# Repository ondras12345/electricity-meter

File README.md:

# Electricity meter
An STM32-based datalogger for electricity meters with pulse LED.

This repository contains both the PCB design files and firmware source code.

## Features
- detecting pulses of LED more than 100 mm away from the sensor,
- dynamic adjustment of bright / dark threshold,
- logging over one year of 1 minute resolution data to SPI flash,
- command line interface for debugging and reading logged data over USB CDC,
- support for RS485 communication.

## Building
### Hardware
I milled the single sided PCB on my [CNC machine](https://github.com/ondras12345/CNC).

Some notes:
- The DCF-3850N connector is only there for future-proofing. I don't currently
  use it and never tested it.
- The onewire bus connector is currently unused, but it should be easy enough
  to add DS18B20 temperature sensors.
- DS3231 RTC is necessary because the internal RTC on my STM32F103 was not
  accurate enough. Cut JP1 (battery power to STM32 VBAT) if you decide to use
  it too.
- The micro USB connector was a bad idea. I ended up replacing it with wires
  soldered directly to the board after accidentally breaking it off several
  times.

### Firmware
```sh
make help  # show available commands
make  # build
make check  # run cppcheck
```

For uploading to the STM32 via STlink, I use `tools/mkbin` and
`tools/upload_latest`.

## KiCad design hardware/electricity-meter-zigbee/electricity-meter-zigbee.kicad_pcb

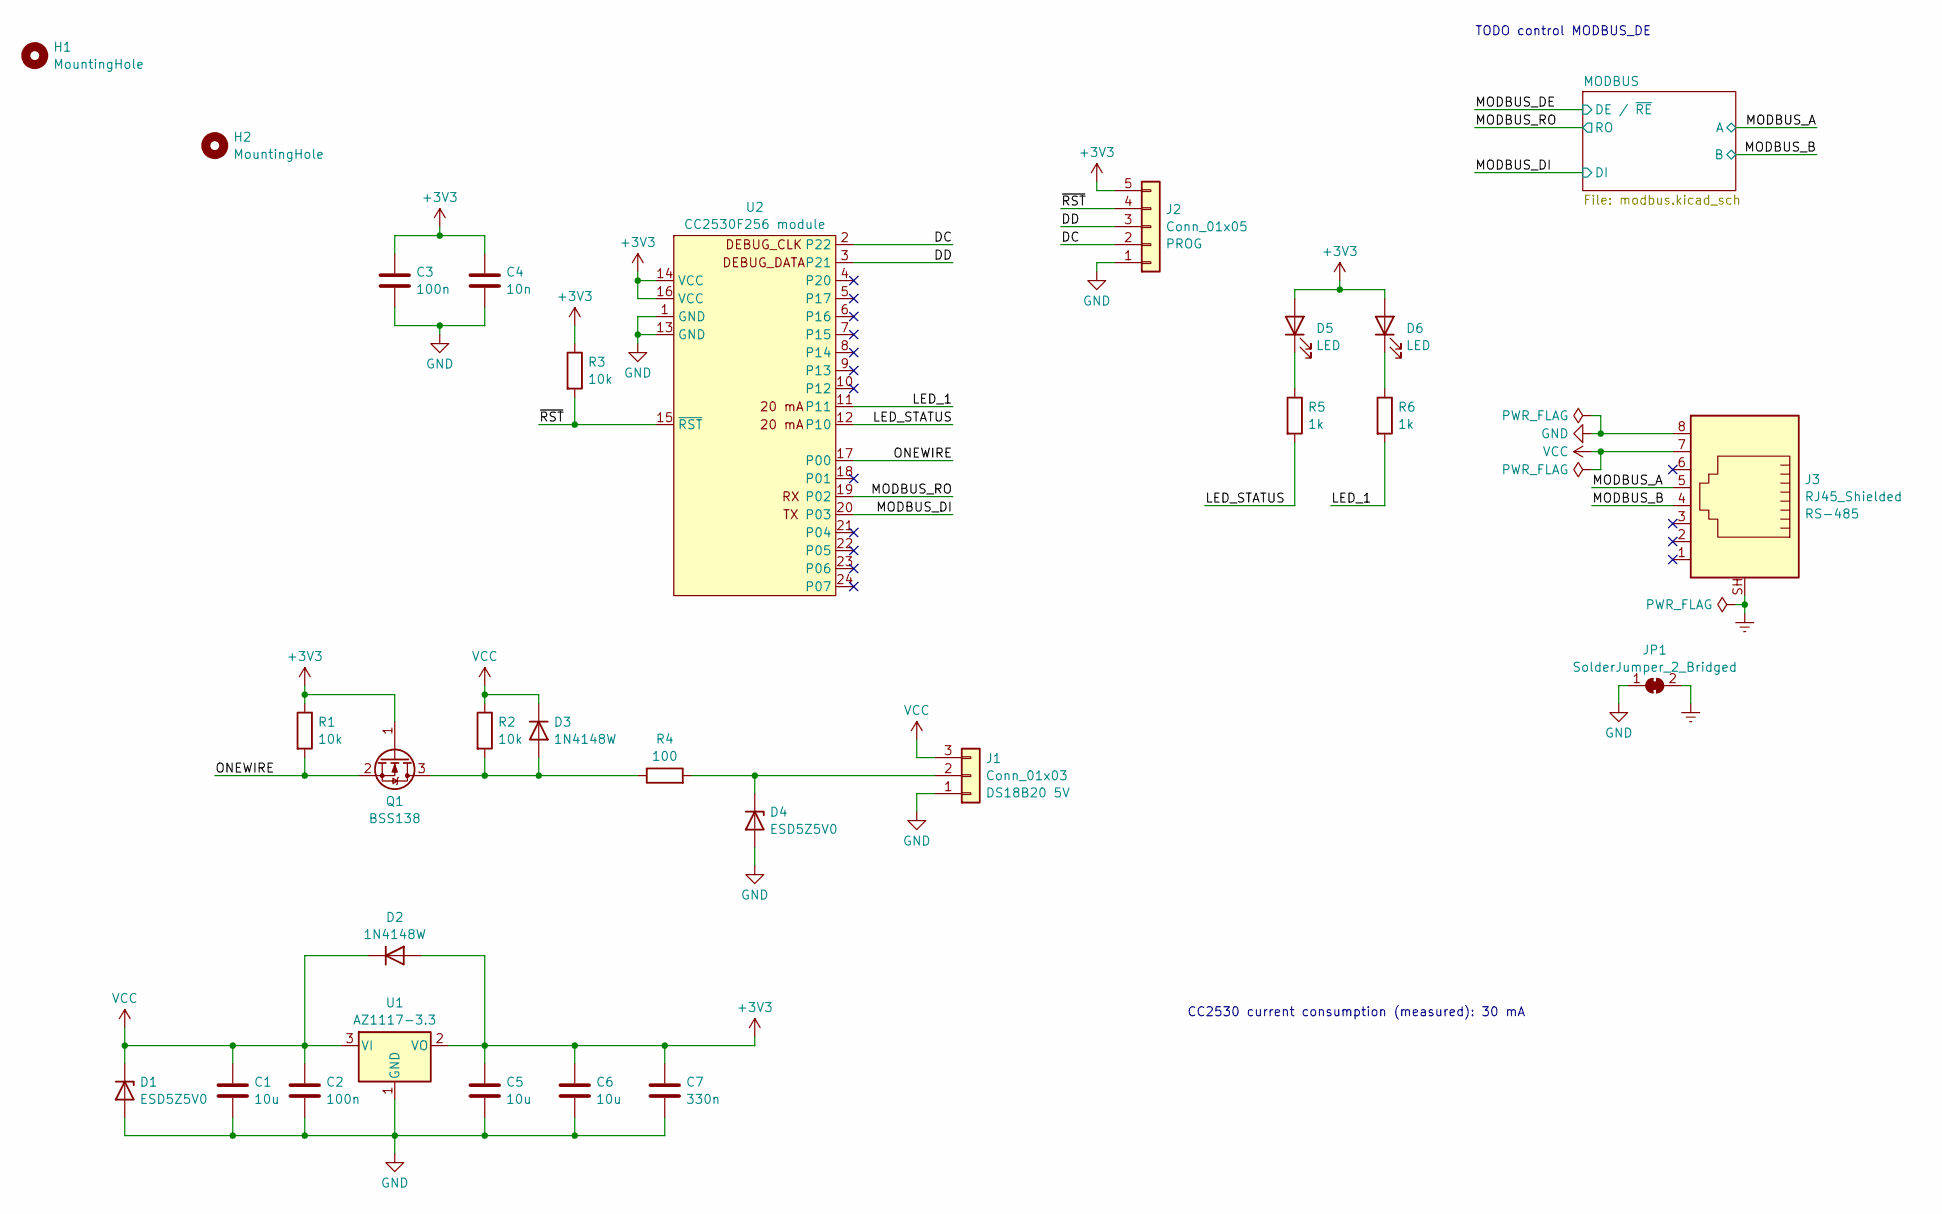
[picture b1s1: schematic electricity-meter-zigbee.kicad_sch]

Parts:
C1, C5, C6: 10u; C_1206_3216Metric_Pad1.33x1.80mm_HandSolder
C2, C3: 100n; C_1206_3216Metric_Pad1.33x1.80mm_HandSolder
C4: 10n; C_1206_3216Metric_Pad1.33x1.80mm_HandSolder
C7: 330n; C_1206_3216Metric_Pad1.33x1.80mm_HandSolder
D1, D4: ESD5Z5V0; D_SOD-523
D2, D3: 1N4148W; D_SOD-123
D5, D6: LED; LED_D3.0mm
H1, H2: MountingHole; MountingHole_3.2mm_M3
J1: Conn_01x03; Molex_KK-254_AE-6410-03A_1x03_P2.54mm_Vertical
J2: Conn_01x05; Molex_KK-254_AE-6410-05A_1x05_P2.54mm_Vertical
J3: RJ45_Shielded; RJ45_HALO_HFJ11-x2450HRL_Horizontal
JP1: SolderJumper_2_Bridged; SolderJumper-2_P1.3mm_Bridged_RoundedPad1.0x1.5mm
Q1: BSS138; SOT-23
R1, R2, R3: 10k; R_1206_3216Metric_Pad1.30x1.75mm_HandSolder
R4: 100; R_1206_3216Metric_Pad1.30x1.75mm_HandSolder
R5, R6: 1k; R_1206_3216Metric_Pad1.30x1.75mm_HandSolder
U1: AZ1117-3.3; SOT-223-3_TabPin2
U2: CC2530F256 module; CC2530F256_module

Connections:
+3V3: C3.1, C4.1, C5.1, C6.1, C7.1, D2.2 (A), D5.2 (A), D6.2 (A), J2.5, Q1.1 (G), R1.1, R3.1, U1.2 (VO), U2.14 (VCC), U2.16 (VCC); also elsewhere on the board
/DC: J2.2, U2.2 (P22)
/DD: J2.3, U2.3 (P21)
/LED_1: R6.2, U2.11
/LED_STATUS: R5.2, U2.12 (P10)
/MODBUS_A: J3.5; also elsewhere on the board
/MODBUS_B: J3.4; also elsewhere on the board
/MODBUS_DI: U2.20 (P03); also elsewhere on the board
/MODBUS_RO: U2.19 (P02); also elsewhere on the board
/ONEWIRE: Q1.2 (S), R1.2, U2.17 (P00)
/~RST: J2.4, R3.2, U2.15 (~RST)
Earth: J3.SH, JP1.2 (B)
GND: C1.2, C2.2, C3.2, C4.2, C5.2, C6.2, C7.2, D1.2 (A), D4.2 (A), J1.1, J2.1, J3.8, JP1.1 (A), U1.1 (GND), U2.1 (GND), U2.13 (GND); also elsewhere on the board
unnamed: D3.2 (A), Q1.3 (D), R2.2, R4.1
unnamed: D4.1 (K), J1.2, R4.2
unnamed: D5.1 (K), R5.1
unnamed: D6.1 (K), R6.1
VCC: C1.1, C2.1, D1.1 (K), D2.1 (K), D3.1 (K), J1.3, J3.7, R2.1, U1.3 (VI)

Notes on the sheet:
TODO control MODBUS_DE
CC2530 current consumption (measured): 30 mA

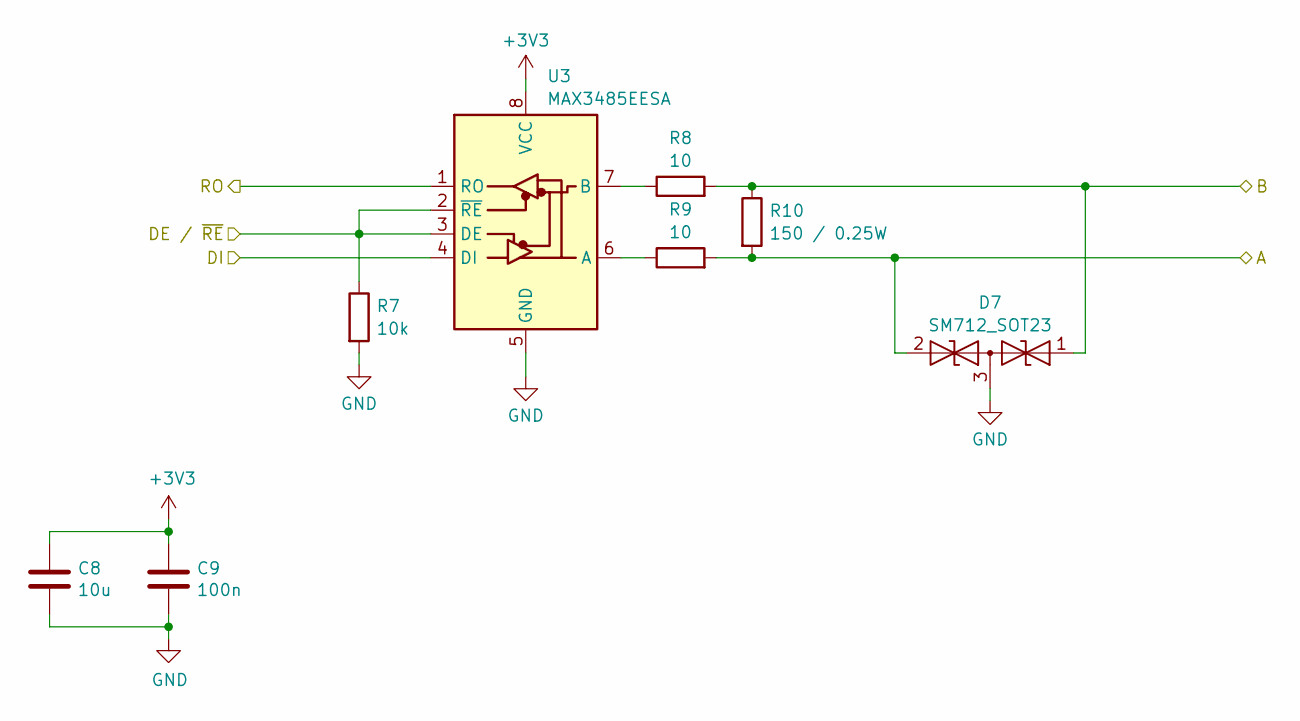
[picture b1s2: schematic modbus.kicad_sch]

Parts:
C8: 10u; C_1206_3216Metric_Pad1.33x1.80mm_HandSolder
C9: 100n; C_1206_3216Metric_Pad1.33x1.80mm_HandSolder
D7: SM712_SOT23; SOT-23
R7: 10k; R_1206_3216Metric_Pad1.30x1.75mm_HandSolder
R8, R9: 10; R_1206_3216Metric_Pad1.30x1.75mm_HandSolder
R10: 150 / 0.25W; R_1206_3216Metric_Pad1.30x1.75mm_HandSolder
U3: MAX3485EESA; SO-8_3.9x4.9mm_P1.27mm

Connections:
+3V3: C8.1, C9.1, U3.8 (VCC); also elsewhere on the board
/MODBUS_A: D7.2 (A2), R9.2, R10.2; also elsewhere on the board
/MODBUS_B: D7.1 (A1), R8.2, R10.1; also elsewhere on the board
/MODBUS_DE: R7.1, U3.2 (~RE), U3.3 (DE)
/MODBUS_DI: U3.4 (DI); also elsewhere on the board
/MODBUS_RO: U3.1 (RO); also elsewhere on the board
GND: C8.2, C9.2, D7.3 (common), R7.2, U3.5 (GND); also elsewhere on the board
unnamed: R9.1, U3.6 (A)
unnamed: R8.1, U3.7 (B)

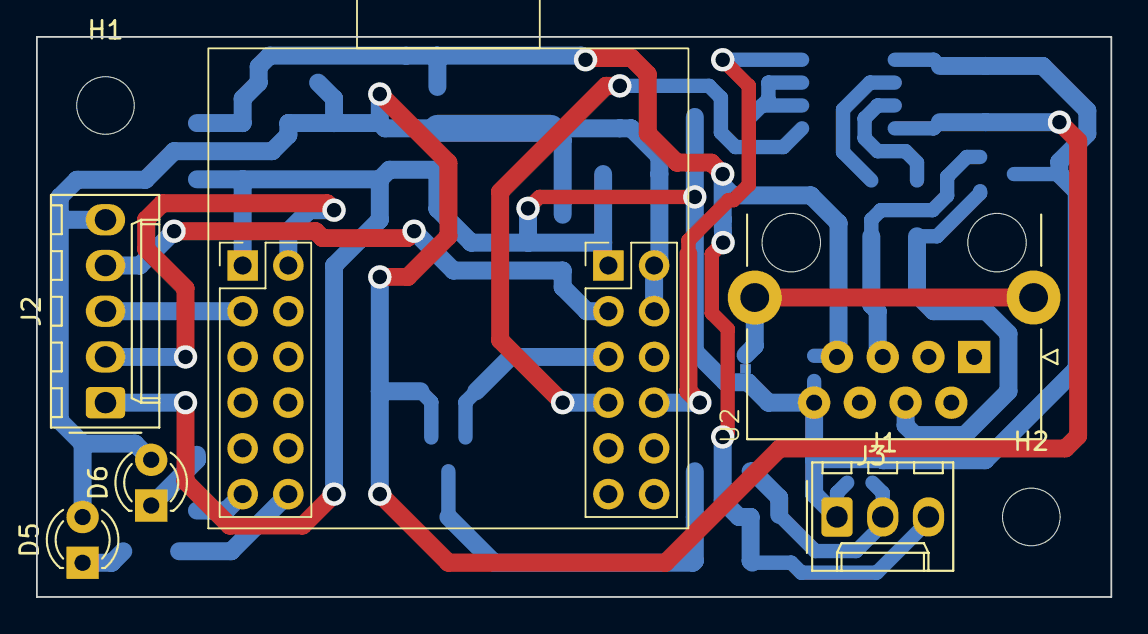
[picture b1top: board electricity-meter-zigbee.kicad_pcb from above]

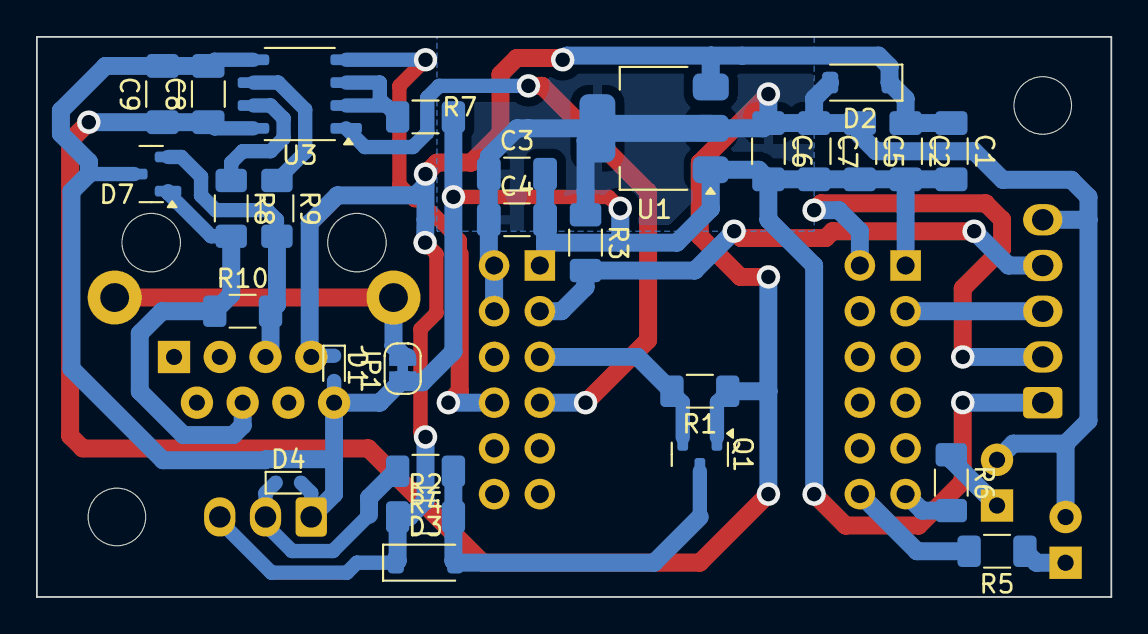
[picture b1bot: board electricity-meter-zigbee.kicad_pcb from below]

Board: 2 copper layers, 59.7 x 31.1 mm, 36 parts (28 on the bottom side), 21 nets.

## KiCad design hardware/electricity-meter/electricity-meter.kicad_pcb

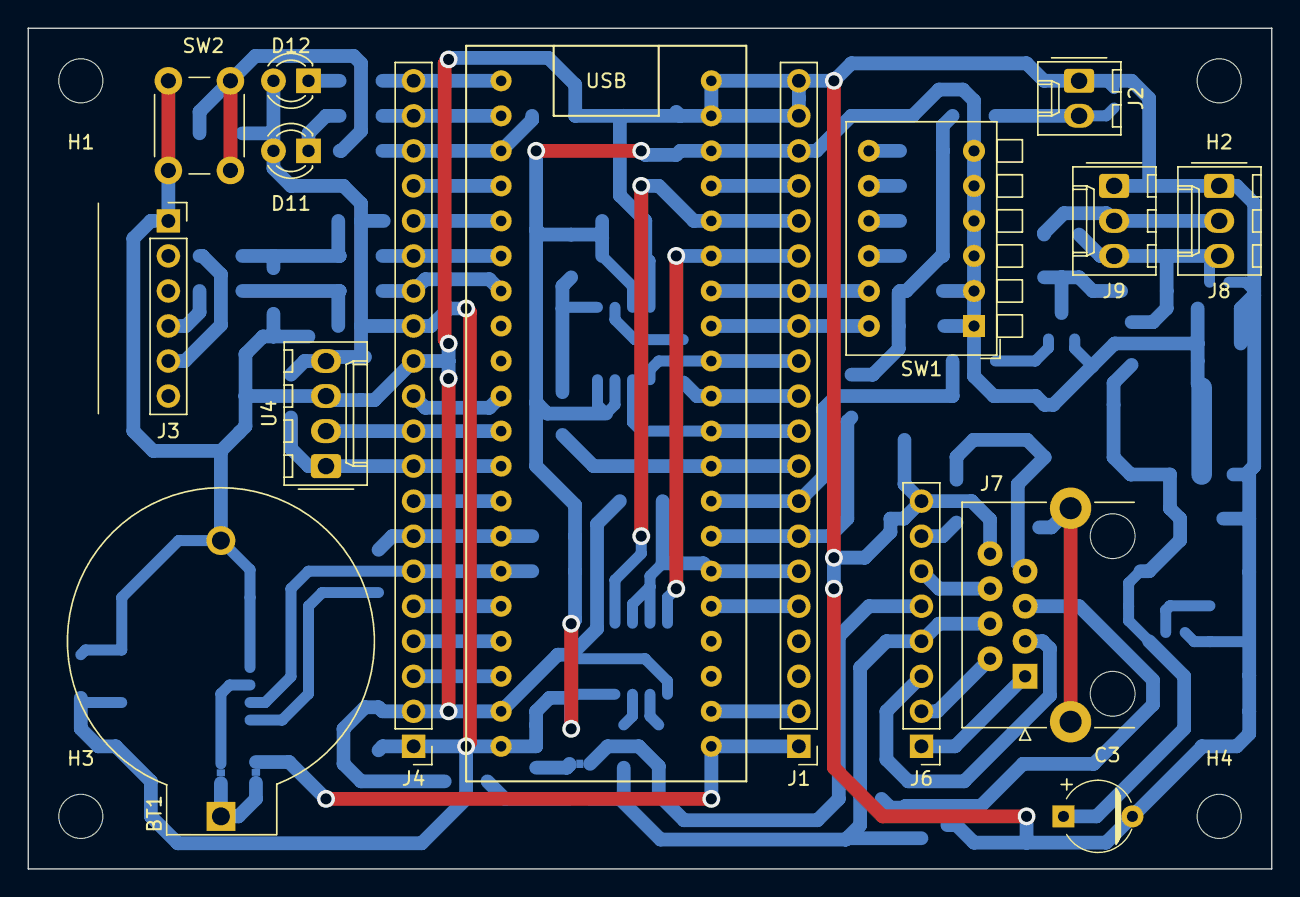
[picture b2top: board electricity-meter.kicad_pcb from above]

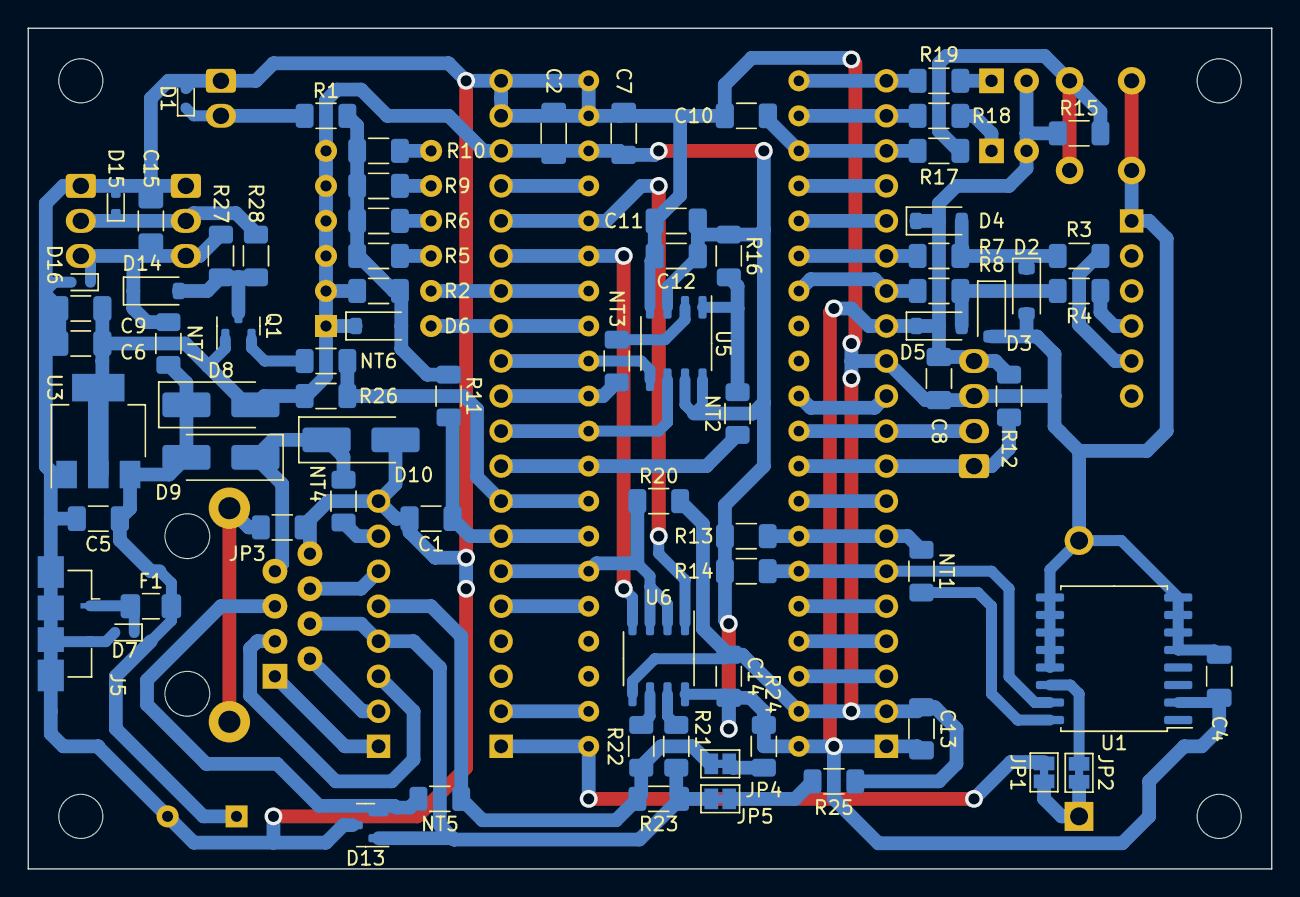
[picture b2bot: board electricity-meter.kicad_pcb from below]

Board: 2 copper layers, 90.2 x 61.0 mm, 95 parts (75 on the bottom side), 71 nets.

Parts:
BT1: CR2032; BatteryHolder_DS1092-04-B6P
C1: 10n; C_1206_3216Metric_Pad1.33x1.80mm_HandSolder
C2, C4, C5, C8, C10, C12, C14, C15: 100n; C_1206_3216Metric_Pad1.33x1.80mm_HandSolder
C3: 100u; CP_Radial_D5.0mm_P5.00mm
C6, C7, C11, C13: 10u; C_1206_3216Metric_Pad1.33x1.80mm_HandSolder
C9: 330n; C_1206_3216Metric_Pad1.33x1.80mm_HandSolder
D1: ESD5Z3.3T1G; D_SOD-523
D2, D3, D4, D5, D6, D14: 1N4148W; D_SOD-123
D7, D15, D16: ESD5Z5V0; D_SOD-523
D8, D9, D10: 1N4007; D_SMA_Handsoldering
D11: YELLOW; LED_D3.0mm
D12: GREEN; LED_D3.0mm
D13: SM712_SOT23; SOT-23
F1: 0ZCJ0016FF2E; Fuse_1206_3216Metric_Pad1.42x1.75mm_HandSolder
H1, H2, H3, H4: MountingHole; MountingHole_3.2mm_M3
J1, J4: Conn_01x20_Pin; PinHeader_1x20_P2.54mm_Vertical
J2: Conn_01x02_Pin; Molex_KK-254_AE-6410-02A_1x02_P2.54mm_Vertical
J3: FTDI breakout; FTDI_breakout
J5: ESB228110100Z; USB_Micro-B_Amphenol_10104110_Horizontal_power_only
J6: Conn_01x08; PinHeader_1x08_P2.54mm_Vertical
J7: RJ45_Shielded; RJ45_HALO_HFJ11-x2450HRL_Horizontal
J8, J9: Conn_01x03; Molex_KK-254_AE-6410-03A_1x03_P2.54mm_Vertical
JP1, JP2, JP4, JP5: SolderJumper_2_Bridged; SolderJumper-2_P1.3mm_Bridged_Pad1.0x1.5mm
JP3: SolderJumper_2_Bridged; R_1206_3216Metric_Pad1.30x1.75mm_HandSolder
NT1, NT2, NT3, NT4, NT5, NT6, NT7: NetTie_2; R_1206_3216Metric_Pad1.30x1.75mm_HandSolder
Q1: BSS138; SOT-23
R1, R3, R4: 1k; R_1206_3216Metric_Pad1.30x1.75mm_HandSolder
R2, R5: 330k; R_1206_3216Metric_Pad1.30x1.75mm_HandSolder
R6: 100k; R_1206_3216Metric_Pad1.30x1.75mm_HandSolder
R7, R8: 100; R_1206_3216Metric_Pad1.30x1.75mm_HandSolder
R9: 33k; R_1206_3216Metric_Pad1.30x1.75mm_HandSolder
R10, R12, R15, R16, R17, R20, R26, R27: 10k; R_1206_3216Metric_Pad1.30x1.75mm_HandSolder
R11, R18, R19, R24, R25: 330; R_1206_3216Metric_Pad1.30x1.75mm_HandSolder
R13, R14: 2k2; R_1206_3216Metric_Pad1.30x1.75mm_HandSolder
R21, R22, R28: 10; R_1206_3216Metric_Pad1.30x1.75mm_HandSolder
R23: 150 / 0.25W; R_1206_3216Metric_Pad1.30x1.75mm_HandSolder
SW1: SW_DIP_x06; SW_DIP_SPSTx06_Piano_10.8x16.8mm_W7.62mm_P2.54mm
SW2: SW_Push; SW_PUSH_6mm
U1: DS3231M; SOIC-16W_7.5x10.3mm_P1.27mm
U2: ChinaBluePill
U3: AZ1117-3.3; SOT-223-3_TabPin2
U4: DCF-3850N-800; Molex_KK-254_AE-6410-04A_1x04_P2.54mm_Vertical
U5: MX25L3233FM1; SOP-8_3.9x4.9mm_P1.27mm
U6: MAX3485EESA; SO-8_3.9x4.9mm_P1.27mm

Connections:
+3V3: C2.1, C4.1, C6.1, C7.1, C8.1, C9.1, C11.1, C12.1, C13.1, C14.1, D4.1 (K), D5.1 (K), D6.1 (K), D8.2 (A), D11.2 (A), D12.2 (A), J1.18, J4.1, J4.13, Q1.1 (G), R2.1, R12.1, R13.1, R14.1, R15.1, R16.1, R24.1, R26.1, SW1.1, SW1.2, SW1.3, SW1.4, SW1.5, SW1.6, U1.2 (VCC), U2.3V3, U3.2 (VO), U4.4 (VDD), U5.3 (~WP/SIO2), U5.7 (~HOLD/SIO3), U5.8 (VCC), U6.8 (VCC)
+5V: C3.1, C5.1, D8.1 (K), D9.2 (A), F1.2, NT7.2, U3.3 (VI)
/5V_STM: J4.3, U2.5V
/BTN_UMOUNT: C10.1, J4.18, R17.1, U2.PB14
/DCF77_DATA: J4.10, U2.PB3, U4.2 (OUT)
/DCF77_~PON: J4.9, R12.2, U2.PB4, U4.1 (~PON)
/LED_PULSE: J4.19, R18.2, U2.PB13
/LED_STATUS: J4.20, R19.2, U2.PB12
/MISO: J1.11, NT3.1, U2.PA6
/MODBUS_A: D13.2 (A2), J7.5, NT5.2
/MODBUS_A_NT: J6.5, JP4.1 (A), NT5.1, R22.2, R23.2
/MODBUS_B: D13.1 (A1), J6.4, J7.4, JP5.2 (B), R21.2, R23.1
/MODBUS_DE: J1.6, R20.1, U2.PA1, U6.2 (~RE), U6.3 (DE)
/MODBUS_DI: J1.15, U2.PB10, U6.4 (DI)
/MODBUS_RO: J1.16, U2.PB11, U6.1 (RO)
/MODBUS_VP: D9.1 (K), D10.1 (K), J7.7, NT4.2
/MOSI: J1.12, U2.PA7, U5.5 (SI/SIO0)
/NRST: J1.17, U2.NRST
/ONEWIRE: J1.8, NT6.1, R26.2, U2.PA3
/PA0: J1.5, U2.PA0
/PA2: C1.1, J1.7, R11.2, U2.PA2
/PA4: J1.9, NT2.1, U2.PA4
/PA5: J1.10, U2.PA5, U5.6 (SCLK)
/PA8: J4.16, U2.PA8
/PA9: J4.15, R7.2, U2.PA9
/PA10: J4.14, R8.2, U2.PA10
/PA15: J4.11, U2.PA15
/PB0: J1.13, SW1.12, U2.PB0
/PB1: J1.14, SW1.11, U2.PB1
/PB5: J4.8, U2.PB5
/PB6: J4.7, NT1.1, R13.2, U2.PB6
/PB7: J4.6, R14.2, U1.15 (SDA), U2.PB7
/PB8: J4.5, U2.PB8
/PB9: J4.4, U2.PB9
/PB15: J4.17, U2.PB15
/PC13: J1.2, U2.PC13
/VBAT: J1.1, JP1.2 (B), U2.VBAT
/onewire/ONEWIRE_5V: D14.2 (A), Q1.3 (D), R27.2, R28.1
Earth: J7.SH, JP3.2 (B)
GND: BT1.2 (-), C1.2, C2.2, C3.2, C4.2, C5.2, C6.2, C7.2, C8.2, C9.2, C10.2, C11.2, C12.2, C13.2, C14.2, C15.2, D1.2 (A), D2.2 (A), D3.2 (A), D7.2 (A), D10.2 (A), D13.3 (common), D15.2 (A), D16.2 (A), J1.19, J1.20, J2.1, J3.1 (GND), J4.2, J4.12, J5.5 (GND), J5.6 (Shield), J6.8, J7.8, J8.1, J9.1, JP3.1 (A), R20.2, R25.2, SW2.2, U1.5 (GND), U1.6 (GND), U1.7 (GND), U1.8 (GND), U1.9 (GND), U1.10 (GND), U1.11 (GND), U1.12 (GND), U1.13 (GND), U2.GND, U3.1 (GND), U4.3 (GND), U5.4 (GND), U6.5 (GND)
unnamed: BT1.1 (+), JP1.1 (A), JP2.1 (A)
unnamed: D1.1 (K), J2.2, R1.1
unnamed: D2.1 (K), D4.2 (A), R3.2, R7.1
unnamed: D3.1 (K), D5.2 (A), R4.2, R8.1
unnamed: D6.2 (A), R1.2, R2.2, R5.2, R6.2, R9.2, R10.2, R11.1
unnamed: D7.1 (K), F1.1, J5.1 (VBUS)
unnamed: D11.1 (K), R18.1
unnamed: D12.1 (K), R19.1
unnamed: C15.1, D14.1 (K), D16.1 (K), J8.3, J9.3, NT7.1, R27.1
unnamed: D15.1 (K), J8.2, J9.2, R28.2
unnamed: J3.5 (RX), R3.1
unnamed: J3.4 (TX), R4.1
unnamed: J6.1, J7.1
unnamed: J6.2, J7.2
unnamed: J6.3, J7.3
unnamed: J6.6, J7.6
unnamed: J6.7, NT4.1
unnamed: JP2.2 (B), U1.14 (VBAT)
unnamed: JP4.2 (B), R24.2
unnamed: JP5.1 (A), R25.1
unnamed: NT6.2, Q1.2 (S)
unnamed: R5.1, SW1.10
unnamed: R6.1, SW1.9
unnamed: R9.1, SW1.8
unnamed: R10.1, SW1.7
unnamed: R15.2, R17.2, SW2.1
unnamed: NT1.2, U1.16 (SCL)
unnamed: NT3.2, U5.2 (SO/SIO1)
unnamed: NT2.2, R16.2, U5.1 (~CS)
unnamed: R22.1, U6.6 (A)
unnamed: R21.1, U6.7 (B)

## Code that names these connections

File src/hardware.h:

#pragma once
#include <Arduino.h>

#define PIN_DIP_SW_1 PB0
#define PIN_DIP_SW_2 PB1

#define PIN_LED_STATUS PB12
#define PIN_LED_PULSE PB13
#define PIN_LED_FILTERED PC13

#define PIN_BTN_1 PB14

// see also platformio.ini
#define PIN_RS485_DE PA1

#define PIN_SPI_SS_FLASH PA4
#define PIN_PULSE_COUNTER PA2

#define ADC_RESOLUTION_BITS 12


// LEDs are active low
#define LED_STATUS(state) digitalWrite(PIN_LED_STATUS, !state)
#define LED_PULSE(state) digitalWrite(PIN_LED_PULSE, !state)
#define LED_FILTERED(state) digitalWrite(PIN_LED_FILTERED, !state)

#define BUTTON_1 (!digitalRead(PIN_BTN_1))
#define SWITCH_DIP_1 digitalRead(PIN_DIP_SW_1)
#define SWITCH_DIP_2 digitalRead(PIN_DIP_SW_2)

void hardware_init();

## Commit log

2022-12-24 Add project files
2022-12-25 Change debounce settings
2022-12-25 Increase logging frequency
2022-12-29 [WIP] CLI; does not work
2023-01-04 Simplify config to fit in RAM
2023-01-04 Add tools for upload on ntb1
2023-01-23 Add conf option to dump and rm file
2023-01-23 Fix file conf
2023-01-23 Try to fix slow response of conf menu
2023-01-23 Perform line ending conversion when dumping file
2023-01-23 Remove redundant assignments (cppcheck)
2023-08-17 Close and reopen file at noon
2023-08-20 Add notes for v2
2023-08-20 Add notes about SPI flash
2023-09-13 Add hardware designs
2023-09-15 Update hardware designs
    * LED colors
    * fix net ties excluded from ibom
2023-09-16 Remove v1 firmware
2023-09-16 Add first version of v2 firmware
2023-09-16 Fix shellminator banner buffer too short
2023-09-16 Fix datalogger too_late ms off by a factor of 10
2023-09-16 Improve CLI pulse debug command
2023-09-16 Fix analogpulse validity threshold
2023-09-16 Slow down boot to give USB CDC time to initialize
2023-09-16 Increase pulse_counter min amplitude
2023-09-16 Increase ADC resolution
2023-09-16 Increase pulse_counter min_amplitude
2023-09-16 Fix logic error in analogpulse
2023-09-16 Fix rtc CLI command
2023-09-17 Print more human-friendly numbers in CLI pulse
2023-09-17 Add SerialFlash support to datalogger
2023-10-05 Add CLI command for datalogger file dump
2023-10-06 Fix datalogger SPI flash comms
2023-10-06 Fix endless binary search in datalogger.cpp
2023-10-06 Fix time sprintf in cli.cpp
2023-10-06 Fix datalogger record index does not advance
2023-10-06 Fix binary search in datalogger.cpp
2023-10-06 Only turn on LEDs if button is pressed
2023-10-07 Use modified RTClib to reduce FLASH usage
    original RTClib
    RAM: [=== ] 26.7% (used 5468 bytes from 20480 bytes)
    Flash: [==========] 95.6% (used 62656 bytes from 65536 bytes)
    modified RTClib
    RAM: [=== ] 25.5% (used 5232 bytes from 20480 bytes)
    Flash: [========= ] 89.2% (used 58432 bytes from 65536 bytes)
2023-10-07 Reduce FLASH usage
    before
    RAM: [=== ] 25.5% (used 5232 bytes from 20480 bytes)
    Flash: [========= ] 89.2% (used 58432 bytes from 65536 bytes)
    shellminator w/o high memory
    RAM: [== ] 24.8% (used 5076 bytes from 20480 bytes)
    Flash: [========= ] 89.0% (used 58320 bytes from 65536 bytes)
2023-10-07 Report data via RS485
2023-10-07 Enable watchdog
2023-10-07 Update TODO comments
2023-10-07 Fix cppcheck warnings in RTClib
2023-10-07 Make datalogger struct packed
    sizeof datalogger_record_t has gone down from 8 to 6.
2023-10-07 Fix RS485 report sent too often
2023-10-08 Increase Serial TX buffer size
    RS485 reporting sends long messages with slow baud rate.
    This should help prevent it from blocking for too long.
    before:
    RAM: [=== ] 26.4% (used 5412 bytes from 20480 bytes)
    Flash: [========= ] 93.2% (used 61068 bytes from 65536 bytes)
    after:
2023-10-08 Revert "Fix cppcheck warnings in RTClib"
    This reverts commit 63e236840ac3ef4d5ee0f4298fe5c1f083559317.
2023-10-08 Add millis()-based RTC to measure LSE clock drift
2023-10-16 Use external RTC
2023-10-16 Fix program does not fit in FLASH
2023-10-17 Use newer framework to reduce FLASH utilization
    15.4.1: overflowed by 684 bytes
    16.0.0: Flash: [==========] 99.4% (used 65148 bytes from 65536 bytes)
    17.0.0: Flash: [==========] 99.1% (used 64932 bytes from 65536 bytes)
2023-11-04 Disable RS485 with DIP switch
    This should lower power consumption in datalogger-only mode.
2023-11-09 Add workaround for USB CDC losing data
2024-01-09 Use st-link for upload
2024-01-10 Fix argument parsing in cmnd_datalogger
2024-06-16 Update documentation
2024-06-16 Add LICENSE
2024-07-21 Update libs
    before:
    RAM: [=== ] 32.8% (used 6716 bytes from 20480 bytes)
    Flash: [==========] 99.5% (used 65196 bytes from 65536 bytes)
    ststm32:
    RAM: [=== ] 32.6% (used 6684 bytes from 20480 bytes)
    Flash: [==========] 98.2% (used 64388 bytes from 65536 bytes)
2024-07-21 Improve RS485 messages & reduce power consumption
2024-07-21 Control RS485 report rate via DIP switch
2024-07-21 Add zigbee firmware
2024-07-21 Add hardware designs for electricity-meter-zigbee
2024-07-23 Add info about hardware mod
2024-07-27 Fix RS485 message format
2024-07-27 Allow RS485 DIP switch change without reset
2024-09-08 Reduce min_amplitude threshold
2024-09-08 Change RS485 message format
    Report min and max instead of amplitude; add checksum.
2024-09-08 Update ststm32 platform
2024-09-08 Fix checksum comment
2024-10-20 Update zigbee firmware
